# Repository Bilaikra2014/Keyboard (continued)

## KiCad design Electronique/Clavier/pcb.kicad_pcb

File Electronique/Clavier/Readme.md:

# Partie electronique du clavier
## Gestion d'alimentation et Chargeur Li-Po

Lorsque la batterie est déchargée, le clavier sera branché à l'ordinateur via une prise USB. La prise de l'ordinateur va alimenter le clavier, et charger la batterie avec le courant restant. Une prise USB A d'ordinateur peut fournir en général jusqu'à 500 mA. 

Pour gérer l'alimentation et la charge, le composant utilisé sera le [MCP73871](https://ww1.microchip.com/downloads/en/DeviceDoc/MCP73871-Data-Sheet-20002090E.pdf) qui permet : 
  - **Gestion du Power Path** : Alimente le système depuis l'USB tout en gérant la charge la batterie
  - **Partage du courant** : Donne la priorité à l'alimentation du système, le courant restant est alloué à la charge de la batterie

<div align="center">
</div>

**Alimentation et Puissance**
  - In (18) : Alimentation du composant -> USB
  - Out (20) : Alimentation du système -> Régulateur LDO
  - Vbat (14) : Charge de la batterie -> Vbat
  - Vss (10) : Masse -> GND

**Contrôle et Logique**:
  - SEL (3) : Limite de courant à tirer sur l'USB -> LOW pour 500 mA (HIGH pour 1,8)
  - PROG2 (4) : Courant d'entré max à tirer -> HIGH pour 500 mA (HIGH pour 100mA)  
  - CE (17) : Activation du système à l'état haut -> Vusb
  - TE (9) : Sécurité interne du temps de charge -> GND

**Programmation et Sécurité**:
  - PROG1 (13) : Courant de charge rapide -> R = 1000V/Ireg, on veut Ireg = 250mA donc R = 4k
  - PROG3 (12) : Seuil de fin de charge -> R = 40k
  - VPCC (2)   : 
  - VBAT_S (16): Sonde de tension -> Vbat
  - THERM (5)  : Capteur de temperature ->  

**Indicateurs visuel**: Ces broches tirent vers la masse, on y connecte des leds
  - PG (6)    : Indication que l'USB est branché, à brancher à l'ESP32 pour qu'il detecte si on est sur batterie ou USB
  - STAT1 (8) : Indication de la phase de charge 
  - STAT2 (7) : Indication de la fin de charge 

## Régulateur de tension

Le régulateur de tension utilisé est un [TLV75533PDBV](https://www.ti.com/lit/ds/symlink/tlv755p.pdf). Il a une très faible tension de dropout, 238mV à 500mA.

<div align="center"></div>

## Mesure de la batterie

La mesure de la batterie permet d'indiquer à l'utilisateur si le clavier à besoin d'être chargé ou pas. La tension étant supérieur aux 3v3 de l'esp32, il faut diviser cette tension pour qu'elle puisse être lue par l'esp32 à travers un pont diviseur de tension.

<div align="center"></div>

**Ajout des transistors Q3 et Q4**:

Utiliser simplement un pont diviseur consommerait du courant en permance, ici 13µA. C'est pour cela que des transistors ont été ajouté. Le transistor Q3 est un mosfet canal P, qui lie la batterie au pont diviseur lorsqu'il est passant. Ce transistor est piloté par son complémentaire Q4, un canal N commandé par l'esp32. Ce transistor sera passant uniquement lors de la mesure. La résistance R9 sert de pull-up pour maintenir le transistor Q3 bloqué quand Q4 est bloqué.

## USB-C et protection ESD

Le port USB-C permet l'utilisation filaire du clavier, ainsi que la recharge de la batterie.

<div align="center"></div>

Les broches D+ et D- permettent la communication ESP32-Ordinateur. 
Les broches CC1 et CC2 doivent être liées à des résistances de 5k1 de pull-down pour que la source détecte la présence du clavier et délivre ainsi le 5v.

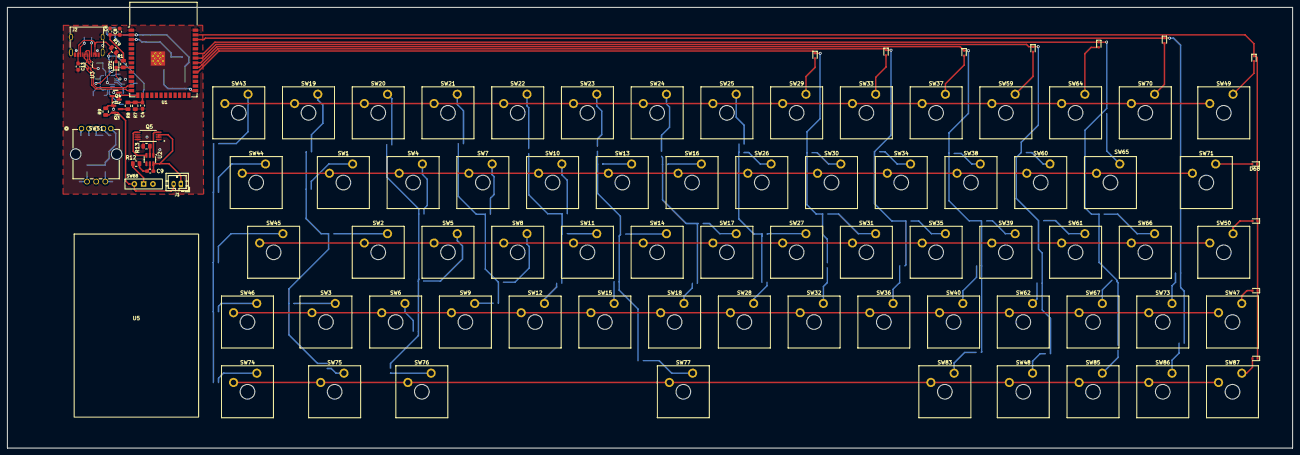
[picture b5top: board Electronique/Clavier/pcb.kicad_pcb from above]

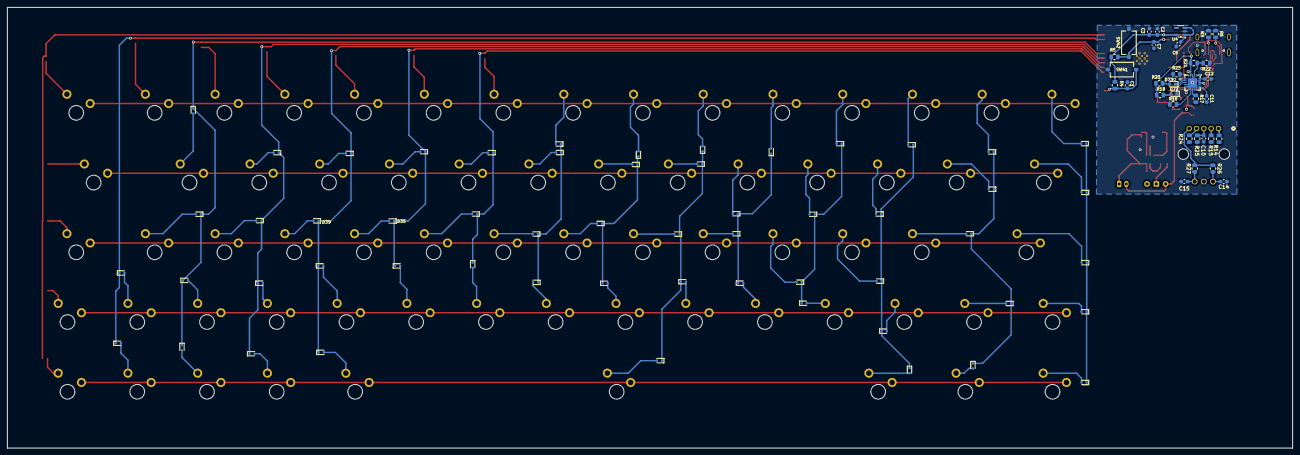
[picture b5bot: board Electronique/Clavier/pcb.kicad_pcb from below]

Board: 4 copper layers, 351.1 x 120.4 mm, 191 parts (89 on the bottom side), 126 nets.

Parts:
C1, C2: 100nF; C_0603_1608Metric_Pad1.08x0.95mm_HandSolder
C3, C13: 10µF; C_0603_1608Metric_Pad1.08x0.95mm_HandSolder
C4, C8: 100n; C_0603_1608Metric_Pad1.08x0.95mm_HandSolder
C5, C6: 10µ; C_0603_1608Metric_Pad1.08x0.95mm_HandSolder
C7: 1µF; C_0603_1608Metric_Pad1.08x0.95mm_HandSolder
C9: 4,7nF; C_0603_1608Metric_Pad1.08x0.95mm_HandSolder
C10, C14, C15: 10n; C_0603_1608Metric_Pad1.08x0.95mm_HandSolder
C11, C12: 4.7µF; C_0603_1608Metric_Pad1.08x0.95mm_HandSolder
D1, D2, D3, D4, D5, D6, D7, D8, D9, D10, D11, D12, D13, D14, D15, D16, D17, D18, D19, D20, D21, D22, D23, D24, D25, D26, D27, D28, D29, D30, D31, D32, D33, D34, D35, D36, D37, D38, D39, D40, D41, D42, D43, D44, D45, D46, D47, D48, D59, D60, D61, D62, D63, D64, D65, D66, D67, D68, D70, D74, D75, D76, D77, D83, D85, D86, D87: 1N4148WT; D_SOD-523
D71, D72, D73: LED; LED_0603_1608Metric
J1: JST_PH_B2B-PH-K_1x02_P2.00mm_Vertical
J2: USB_C_Receptacle_G-Switch_GT-USB-7010ASV
Q3: BSS84; SOT-23
Q4: BSS138; SOT-23
Q5: FS8205A; SOP65P640X120-8N
R1: 10K; R_0805_2012Metric
R3, R6: 5.1k; R_0805_2012Metric
R4, R5, R23, R25, R26, R27: 10k; R_0805_2012Metric
R7: 220k; R_0805_2012Metric
R8, R9, R22: 100k; R_0805_2012Metric
R12: 100; R_0805_2012Metric
R13: 1k; R_0805_2012Metric
R14, R15, R24: 200; R_0805_2012Metric
R16: 20k; R_0805_2012Metric
R17: 2k; R_0805_2012Metric
R18, R19, R20: 470; R_0805_2012Metric
R21: 270k; R_0805_2012Metric
SW1: A; SW_Cherry_MX_Plate_1.00u
SW2: Q; SW_Cherry_MX_Plate_1.00u
SW3: <; SW_Cherry_MX_Plate_1.00u
SW4: Z; SW_Cherry_MX_Plate_1.00u
SW5: S; SW_Cherry_MX_Plate_1.00u
SW6: W; SW_Cherry_MX_Plate_1.00u
SW7: E; SW_Cherry_MX_Plate_1.00u
SW8: D; SW_Cherry_MX_Plate_1.00u
SW9: X; SW_Cherry_MX_Plate_1.00u
SW10: R; SW_Cherry_MX_Plate_1.00u
SW11: F; SW_Cherry_MX_Plate_1.00u
SW12: C; SW_Cherry_MX_Plate_1.00u
SW13: T; SW_Cherry_MX_Plate_1.00u
SW14: G; SW_Cherry_MX_Plate_1.00u
SW15: V; SW_Cherry_MX_Plate_1.00u
SW16: Y; SW_Cherry_MX_Plate_1.00u
SW17: H; SW_Cherry_MX_Plate_1.00u
SW18: B; SW_Cherry_MX_Plate_1.00u
SW19: 1; SW_Cherry_MX_Plate_1.00u
SW20: 2; SW_Cherry_MX_Plate_1.00u
SW21: 3; SW_Cherry_MX_Plate_1.00u
SW22: 4; SW_Cherry_MX_Plate_1.00u
SW23: 5; SW_Cherry_MX_Plate_1.00u
SW24: 6; SW_Cherry_MX_Plate_1.00u
SW25: 7; SW_Cherry_MX_Plate_1.00u
SW26: U; SW_Cherry_MX_Plate_1.00u
SW27: J; SW_Cherry_MX_Plate_1.00u
SW28: N; SW_Cherry_MX_Plate_1.00u
SW29: 8; SW_Cherry_MX_Plate_1.00u
SW30: I; SW_Cherry_MX_Plate_1.00u
SW31: K; SW_Cherry_MX_Plate_1.00u
SW32: ,; SW_Cherry_MX_Plate_1.00u
SW33: 9; SW_Cherry_MX_Plate_1.00u
SW34: O; SW_Cherry_MX_Plate_1.00u
SW35: L; SW_Cherry_MX_Plate_1.00u
SW36: ;; SW_Cherry_MX_Plate_1.00u
SW37: 0; SW_Cherry_MX_Plate_1.00u
SW38: P; SW_Cherry_MX_Plate_1.00u
SW39: M; SW_Cherry_MX_Plate_1.00u
SW40: :; SW_Cherry_MX_Plate_1.00u
SW41, SW42: SW_Push; SW_Tactile_SPST_NO_Straight_CK_PTS636Sx25SMTRLFS
SW43: ²; SW_Cherry_MX_Plate_1.00u
SW44: Tab; SW_Cherry_MX_Plate_1.50u
SW45: VMaj; SW_Cherry_MX_Plate_2.00u
SW46: Shift; SW_Cherry_MX_Plate_1.25u
SW47: PageDown; SW_Cherry_MX_Plate_1.00u
SW48: DEF; SW_Cherry_MX_Plate_1.00u
SW49, SW50: Definir; SW_Cherry_MX_Plate_1.25u
SW51: COM-15141; COM-15141_SPK
SW59: ); SW_Cherry_MX_Plate_1.00u
SW60: ^; SW_Cherry_MX_Plate_1.00u
SW61: ù; SW_Cherry_MX_Plate_1.00u
SW62: !; SW_Cherry_MX_Plate_1.00u
SW64: =; SW_Cherry_MX_Plate_1.00u
SW65: $; SW_Cherry_MX_Plate_1.00u
SW66: *; SW_Cherry_MX_Plate_1.00u
SW67: PageUp; SW_Cherry_MX_Plate_1.00u
SW68: SW_Push_SPDT; SW_Slide-03_Wuerth-WS-SLTV_10x2.5x6.4_P2.54mm
SW70: Delete; SW_Cherry_MX_Plate_1.00u
SW71: Entrer; SW_Cherry_MX_Plate_1.75u
SW73: Up; SW_Cherry_MX_Plate_1.00u
SW74: CTRL; SW_Cherry_MX_Plate_1.25u
SW75: Win; SW_Cherry_MX_Plate_1.25u
SW76: Alt; SW_Cherry_MX_Plate_1.25u
SW77: Space; SW_Cherry_MX_Plate_6.25u
SW83: Fn; SW_Cherry_MX_Plate_1.25u
SW85: Left; SW_Cherry_MX_Plate_1.00u
SW86: Down; SW_Cherry_MX_Plate_1.00u
SW87: Right; SW_Cherry_MX_Plate_1.00u
U1: ESP32-S3-WROOM-1
U2: DW01A; SOT-23-6
U3: USBLC6-2P6; SOT-666
U4: TLV75533PDBV; SOT-23-5
U5: Lipo1s
U6: MCP73871-2CC; QFN-20-1EP_4x4mm_P0.5mm_EP2.5x2.5mm

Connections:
+3.3V: C2.2, C3.2, C6.1, C8.1, R1.1, R4.1, R5.1, R26.2, R27.2, SW51.5, U1.2 (3V3), U4.5 (OUT)
BOOT: C1.1, R4.2, SW41.2, U1.27 (IO0)
Check Batt: C4.2, R7.1, R8.2, U1.16 (IO46)
Check Batt En: Q4.1 (G), U1.15 (IO3)
Col1: D43.1 (K), D44.1 (K), D45.1 (K), D46.1 (K), D74.1 (K)
Col2: D1.1 (K), D2.1 (K), D3.1 (K), D19.1 (K), D75.1 (K)
Col3: D4.1 (K), D5.1 (K), D6.1 (K), D20.1 (K), D76.1 (K)
Col4: D7.1 (K), D8.1 (K), D9.1 (K), D21.1 (K)
Col5: D10.1 (K), D11.1 (K), D12.1 (K), D22.1 (K)
Col6: D13.1 (K), D14.1 (K), D15.1 (K), D23.1 (K), D77.1 (K)
Col7: D16.1 (K), D17.1 (K), D18.1 (K), D24.1 (K)
Col8: D25.1 (K), D26.1 (K), D27.1 (K), D28.1 (K)
Col9: D29.1 (K), D30.1 (K), D31.1 (K), D32.1 (K), U1.31 (IO38)
Col10: D33.1 (K), D34.1 (K), D35.1 (K), D36.1 (K), U1.32 (IO39)
Col11: D37.1 (K), D38.1 (K), D39.1 (K), D40.1 (K), D83.1 (K), U1.33 (IO40)
Col12: D42.1 (K), D59.1 (K), D60.1 (K), D61.1 (K), D62.1 (K), U1.34 (IO41)
Col13: D64.1 (K), D65.1 (K), D66.1 (K), D67.1 (K), D85.1 (K), U1.35 (IO42)
Col14: D63.1 (K), D70.1 (K), D86.1 (K), U1.38 (IO2)
Col15: D41.1 (K), D47.1 (K), D48.1 (K), D68.1 (K), D87.1 (K), U1.39 (IO1)
D+: J2.A6 (D+), J2.B6 (D+), U3.3 (I/O2)
D-: J2.A7 (D-), J2.B7 (D-), U3.1 (I/O1)
DP+: U1.14 (USB_D+), U3.4 (I/O2)
DP-: U1.13 (USB_D-), U3.6 (I/O1)
EN: C7.1, R5.2, SW42.2, U1.3 (EN)
GND: C1.2, C2.1, C3.1, C4.1, C5.2, C6.2, C7.2, C8.2, C10.1, C11.2, C12.2, C13.2, C14.1, C15.1, J2.A1 (GND), J2.A12 (GND), J2.B1 (GND), J2.B12 (GND), J2.S1 (SHIELD), Q4.2 (S), Q5.1, Q5.6, Q5.7, Q5.8, R3.2, R6.2, R7.2, R13.2, R16.2, R17.2, R22.1, R23.2, R25.1, SW41.1, SW42.1, SW51.C, U1.1 (GND), U1.40 (GND), U1.41 (GND), U3.2 (GND), U4.2 (GND), U6.3 (SEL), U6.9 (~TE), U6.10 (V_{SS}), U6.11 (V_{SS}), U6.21 (V_{SS})
L1: SW19.1, SW20.1, SW21.1, SW22.1, SW23.1, SW24.1, SW25.1, SW29.1, SW33.1, SW37.1, SW43.1, SW49.1, SW59.1, SW64.1, SW70.1
L2: SW1.1, SW4.1, SW7.1, SW10.1, SW13.1, SW16.1, SW26.1, SW30.1, SW34.1, SW38.1, SW44.1, SW60.1, SW65.1, SW71.1
L3: SW2.1, SW5.1, SW8.1, SW11.1, SW14.1, SW17.1, SW27.1, SW31.1, SW35.1, SW39.1, SW45.1, SW50.1, SW61.1, SW66.1
L4: SW3.1, SW6.1, SW9.1, SW12.1, SW15.1, SW18.1, SW28.1, SW32.1, SW36.1, SW40.1, SW46.1, SW47.1, SW62.1, SW67.1, SW73.1
L5: SW48.1, SW74.1, SW75.1, SW76.1, SW77.1, SW83.1, SW85.1, SW86.1, SW87.1, U1.17 (IO9)
Mute_btn: C10.2, R25.2, SW51.3
unnamed: D1.2 (A), SW1.2
unnamed: D2.2 (A), SW2.2
unnamed: D3.2 (A), SW3.2
unnamed: D4.2 (A), SW4.2
unnamed: D5.2 (A), SW5.2
unnamed: D6.2 (A), SW6.2
unnamed: D7.2 (A), SW7.2
unnamed: D8.2 (A), SW8.2
unnamed: D9.2 (A), SW9.2
unnamed: D10.2 (A), SW10.2
unnamed: D11.2 (A), SW11.2
unnamed: D12.2 (A), SW12.2
unnamed: D13.2 (A), SW13.2
unnamed: D14.2 (A), SW14.2
unnamed: D15.2 (A), SW15.2
unnamed: D16.2 (A), SW16.2
unnamed: D17.2 (A), SW17.2
unnamed: D18.2 (A), SW18.2
unnamed: D19.2 (A), SW19.2
unnamed: D20.2 (A), SW20.2
unnamed: D21.2 (A), SW21.2
unnamed: D22.2 (A), SW22.2
unnamed: D23.2 (A), SW23.2
unnamed: D24.2 (A), SW24.2
unnamed: D25.2 (A), SW25.2
unnamed: D26.2 (A), SW26.2
unnamed: D27.2 (A), SW27.2
unnamed: D28.2 (A), SW28.2
unnamed: D29.2 (A), SW29.2
unnamed: D30.2 (A), SW30.2
unnamed: D31.2 (A), SW31.2
unnamed: D32.2 (A), SW32.2
unnamed: D33.2 (A), SW33.2
unnamed: D34.2 (A), SW34.2
unnamed: D35.2 (A), SW35.2
unnamed: D36.2 (A), SW36.2
unnamed: D37.2 (A), SW37.2
unnamed: D38.2 (A), SW38.2
unnamed: D39.2 (A), SW39.2
unnamed: D40.2 (A), SW40.2
unnamed: D41.2 (A), SW47.2
unnamed: D42.2 (A), SW48.2
unnamed: D43.2 (A), SW43.2
unnamed: D44.2 (A), SW44.2
unnamed: D45.2 (A), SW45.2
unnamed: D46.2 (A), SW46.2
unnamed: D47.2 (A), SW50.2
unnamed: D48.2 (A), SW49.2
unnamed: D59.2 (A), SW59.2
unnamed: D60.2 (A), SW60.2
unnamed: D61.2 (A), SW61.2
unnamed: D62.2 (A), SW62.2
unnamed: D63.2 (A), SW70.2
unnamed: D64.2 (A), SW64.2
unnamed: D65.2 (A), SW65.2
unnamed: D66.2 (A), SW66.2
unnamed: D67.2 (A), SW67.2
unnamed: D68.2 (A), SW71.2
unnamed: D70.2 (A), SW73.2
unnamed: D71.2 (A), R19.2
unnamed: D72.2 (A), R18.2
unnamed: D72.1 (K), U6.8 (STAT1/~LBO)
unnamed: D73.2 (A), R20.2
unnamed: D73.1 (K), U6.7 (STAT2)
unnamed: D74.2 (A), SW74.2
unnamed: D75.2 (A), SW75.2
unnamed: D76.2 (A), SW76.2
unnamed: D77.2 (A), SW77.2
unnamed: D83.2 (A), SW83.2
unnamed: D85.2 (A), SW85.2
unnamed: D86.2 (A), SW86.2
unnamed: D87.2 (A), SW87.2
unnamed: J2.A5 (CC1), R3.1
unnamed: J2.B5 (CC2), R6.1
unnamed: Q3.3 (D), R8.1
unnamed: Q3.1 (G), Q4.3 (D), R9.2
unnamed: R14.2, SW51.1
unnamed: R15.2, SW51.2
unnamed: R24.1, SW51.4
unnamed: R13.1, U2.2 (CS)
unnamed: Q5.5, U2.3 (OC)
unnamed: Q5.4, U2.1 (OD)
unnamed: C9.2, R12.2, U2.5 (VCC)
unnamed: R17.1, U6.13 (PROG1)
unnamed: R16.1, U6.12 (PROG3)
unnamed: R23.1, U6.5 (THERM)
unnamed: R21.2, R22.2, U6.2 (VPCC)
PG: D71.1 (K), R1.2, U1.9 (IO16), U6.6 (~PG)
Valim: C5.1, C12.1, U4.1 (IN), U4.3 (EN), U6.1 (OUT), U6.20 (OUT)
Vbat: C11.1, R12.1, SW68.1 (A), U6.14 (V_{BAT}), U6.15 (V_{BAT}), U6.16 (V_{BAT_SENSE})
Vbat-: C9.1, J1.1, Q5.2, Q5.3, U2.6 (GND)
Vbat_Mes: J1.2, Q3.2 (S), R9.1, SW68.2 (B)
Vol_Down: C15.2, R27.1, SW51.B
Vol_Up: C14.2, R26.1, SW51.A
Vusb: C13.1, J2.A4 (VBUS), J2.A9 (VBUS), J2.B4 (VBUS), J2.B9 (VBUS), R18.1, R19.1, R20.1, R21.1, U3.5 (VBUS), U6.4 (PROG2), U6.17 (CE), U6.18 (IN), U6.19 (IN)

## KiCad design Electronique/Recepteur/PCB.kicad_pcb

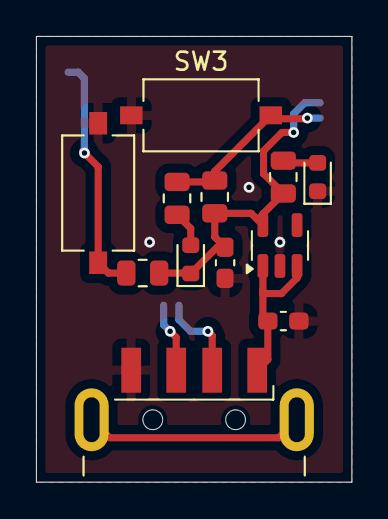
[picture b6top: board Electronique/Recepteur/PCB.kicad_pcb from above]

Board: 2 copper layers, 17.5 x 24.8 mm, 13 parts (1 on the bottom side), 9 nets.

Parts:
C1, C2: 1µ; C_0603_1608Metric_Pad1.08x0.95mm_HandSolder
D4, D5: LED; LED_0603_1608Metric
J1: USB_A; USB_A_CNCTech_1001-011-01101_Horizontal
R2, R3: 470; R_0805_2012Metric
R4, R5: 10k; R_0805_2012Metric
SW3, SW4: SW_Push; SW_Tactile_SPST_NO_Straight_CK_PTS636Sx25SMTRLFS
U3: ESP32-S3-MINI-1; ESP32-S2-MINI-1
U4: TLV75533PDBV; SOT-23-5

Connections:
5V: C2.1, J1.1 (VBUS), U4.1 (IN), U4.3 (EN)
+3.3V: C1.1, D5.1 (K), R3.1, R4.1, R5.1, U3.3 (3V3), U4.5 (OUT)
BOOT: R2.1, R4.2, SW3.2, U3.4 (IO0)
D+: J1.3 (D+), U3.25 (IO21)
D-: J1.2 (D-), U3.24 (USB_D+)
EN (Reset): R5.2, SW4.2, U3.45 (EN)
GND: C1.2, C2.2, D4.1 (K), J1.4 (GND), SW3.1, SW4.1, U3.1 (GND), U3.2 (GND), U3.42 (GND), U3.43 (GND), U3.46 (GND), U3.47 (GND), U3.48 (GND), U3.49 (GND), U3.50 (GND), U3.51 (GND), U3.52 (GND), U3.53 (GND), U3.54 (GND), U3.55 (GND), U3.56 (GND), U3.57 (GND), U3.58 (GND), U3.59 (GND), U3.60 (GND), U3.61 (GND), U3.62 (GND), U3.63 (GND), U3.64 (GND), U3.65 (GND), U4.2 (GND)
unnamed: D4.2 (A), R3.2
unnamed: D5.2 (A), R2.2

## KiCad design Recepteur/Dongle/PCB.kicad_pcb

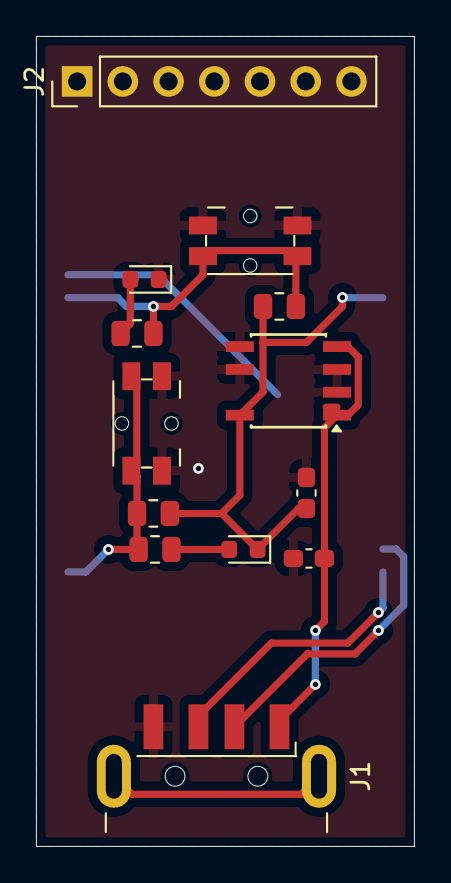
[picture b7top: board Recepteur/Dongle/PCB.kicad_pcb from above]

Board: 2 copper layers, 21.0 x 45.0 mm, 14 parts (1 on the bottom side), 9 nets.

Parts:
C1, C2: 10µ; C_0603_1608Metric_Pad1.08x0.95mm_HandSolder
D4, D5: LED; LED_0603_1608Metric
J1: USB_A; USB_A_CNCTech_1001-011-01101_Horizontal
J2: Conn_01x07; PinHeader_1x07_P2.54mm_Vertical
R2, R3: 470; R_0805_2012Metric
R4, R5: 10k; R_0805_2012Metric
SW3, SW4: SW_Push; Panasonic_EVQPUL_EVQPUC
U2: MAX604; SOIC-8-N7_3.9x4.9mm_P1.27mm
X1: ESP32-S3-WROOM-1-N16R8; ESP32S3WROOM1N8R2

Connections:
+3.3V: C1.1, D5.1 (K), R3.1, R4.1, R5.1, U2.8 (OUT), X1.2 (3V3)
BOOT: R2.1, R4.2, SW3.2, X1.27 (IO0)
D+: J1.3 (D+), X1.14 (IO20)
D-: J1.2 (D-), X1.13 (IO19)
EN (Reset): R5.2, SW4.2, X1.39 (IO1)
GND: C1.2, C2.2, D4.1 (K), J1.4 (GND), SW3.1, SW4.1, U2.2 (GND), U2.3 (GND), U2.5 (SET), U2.6 (GND), X1.1 (GND), X1.40 (GND), X1.41 (GND), X1.42 (GND), X1.43 (GND), X1.44 (GND), X1.45 (GND), X1.46 (GND), X1.47 (GND), X1.48 (GND), X1.49 (GND)
unnamed: D4.2 (A), R3.2
unnamed: D5.2 (A), R2.2
V+: C2.1, J1.1 (VBUS), U2.1 (IN), U2.4 (~OFF)

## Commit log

2025-12-24 création du fichier kicad
2026-01-12 Enhance README with project details and specifications
    Updated project description to include details about the keyboard's power system, microcontroller specifications, and communication protocol.
2026-01-15 Add ESP32 C3 and S3 datasheet links to README
    Added links to ESP32 C3 and S3 datasheets.
2026-01-15 Add ESP32 S3 datasheet link to README
2026-01-15 Add USB C support to ESP32-S3 specifications
    Added USB C support for wired mode in hardware specifications.
2026-01-15 Fix formatting of USB C description in README
2026-01-15 Revise project description and mechanical design details
    Updated project description and clarified mechanical design details.
2026-01-15 update schema
2026-01-16 Update images for ESP32-S3-MINI in README
    Updated images in the README for the ESP32-S3-MINI section.
2026-01-16 update schema & pcb
2026-01-16 Réorganisation de la structure du projet
2026-01-16 Ajout de début de code pour les 2 produits
2026-01-18 Revise project structure in README
    Updated project structure to include new directories for KiCad libraries and clarified existing sections.
2026-01-18 edit schema
2026-01-18 Add initial content to Readme.md
2026-01-18 Update Readme with electronic keyboard details
    Added sections on power management and battery handling.
2026-01-18 Add image for power regulation in keyboard README
    Added an image to illustrate the power regulation and switching mechanism for the keyboard.
2026-01-18 Add image for keyboard power regulation section
    Added an image to illustrate the power regulation and switching mechanism for the keyboard.
2026-01-18 Enhance Readme with LDO and voltage regulation details
    Added details about LDO selection and voltage regulation for the keyboard.
2026-01-24 Update Readme.md with component image
    Added an image to the component summary section.
2026-01-25 Correct MCP73871 component reference in Readme
2026-01-25 Fix link formatting for MCP73871 in Readme.md
2026-01-25 Enhance README with new component details
    Updated the README to include additional details about visual indicators and the addition of transistors Q3 and Q4 for battery voltage measurement.
2026-01-25 update keyboard schematic
2026-01-25 Update Readme with USB-C and ESD protection details
    Added information about USB-C functionality and ESD protection.
2026-02-14 Update project description in README.md
    Removed the term 'bi-mode' from the project description for clarity.
2026-03-21 Add mechanical section to README
2026-03-22 Update voltage regulation description in README
    Clarified voltage regulation details for power sources.
2026-03-29 global update
2026-03-29 remove of clavier_test
2026-04-02 Update README to remove old datasheet links
    Removed outdated datasheet links and added project structure note.
2026-04-02 Revise README for keyboard electronics and matrix design
    Updated the README to reflect changes in the electronic keyboard design, including the matrix layout, ghosting issue, and encoder management.
2026-04-03 Remove communication protocols section from README
    Removed sections on communication protocols including ESP-NOW and USB HID.
2026-04-03 Add communication protocols section to README
    Added sections on wireless and PC communication protocols using ESP-NOW and USB libraries.
2026-04-03 Add README for keyboard functionality
